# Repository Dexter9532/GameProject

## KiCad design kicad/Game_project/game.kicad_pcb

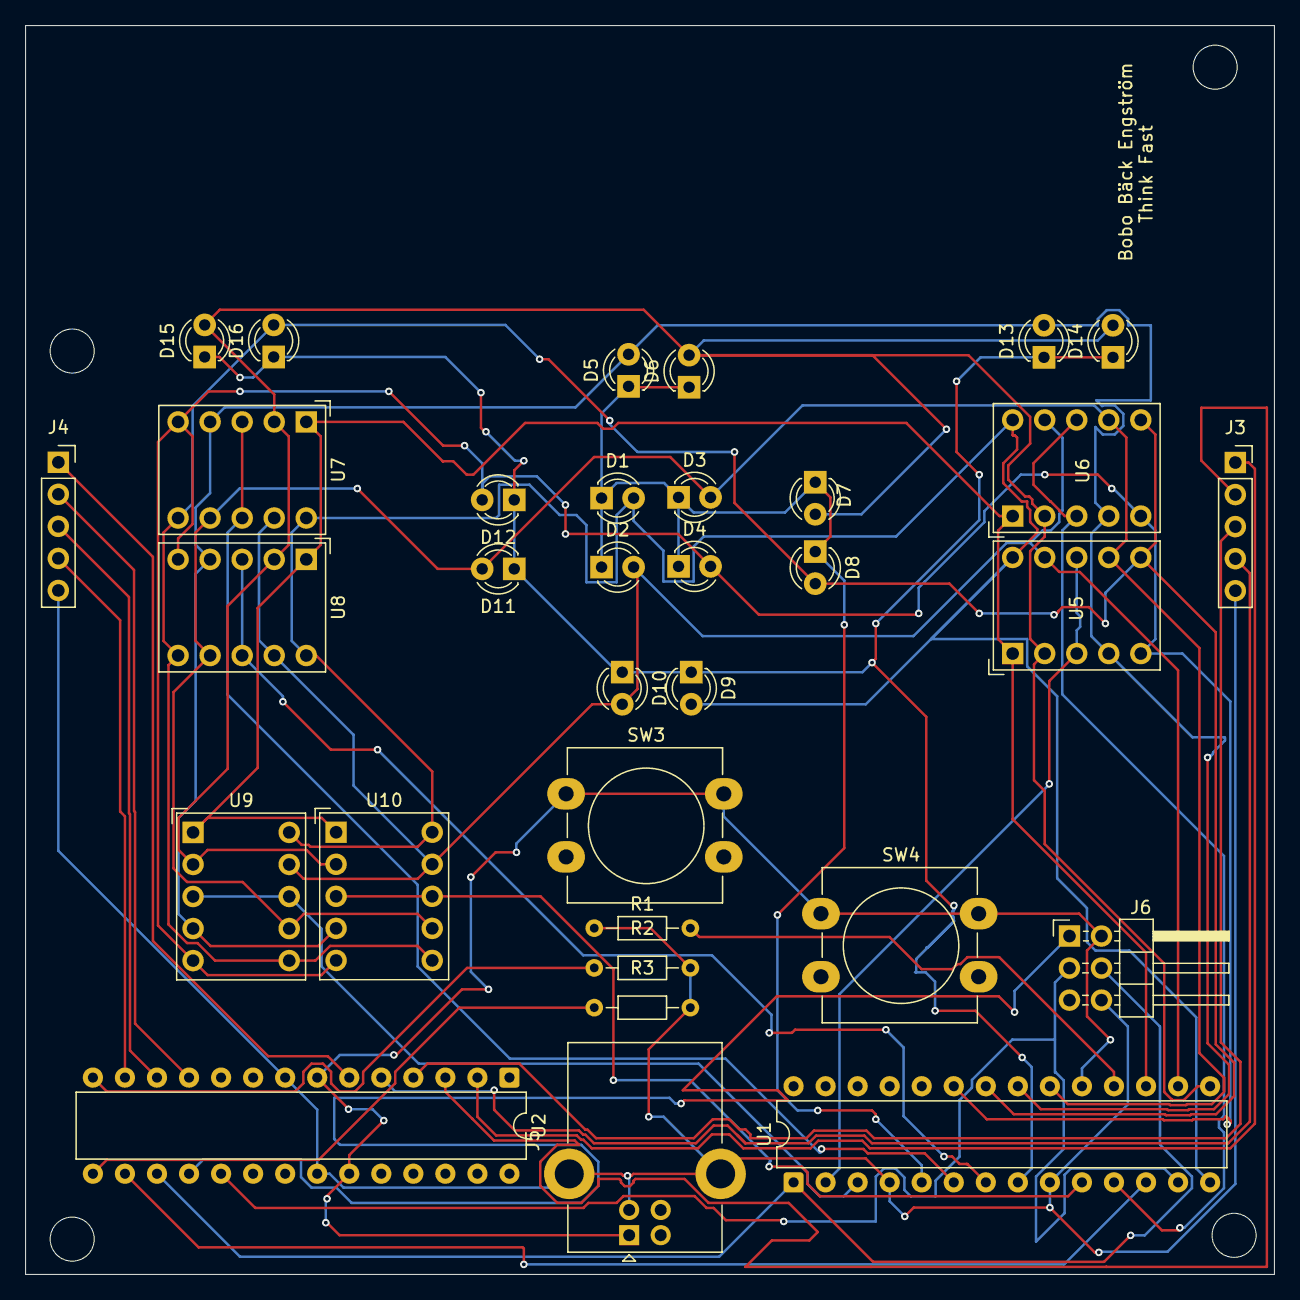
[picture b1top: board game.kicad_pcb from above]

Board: 2 copper layers, 99.0 x 99.0 mm, 33 parts (0 on the bottom side), 33 nets.

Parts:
D1, D2, D3, D4, D5, D6, D7, D8, D9, D10, D11, D12, D13, D14, D15, D16: LED; LED_D3.0mm_Clear
J3, J4: Conn_01x05_Socket; PinSocket_1x05_P2.54mm_Vertical
J5: USB_B; USB_B_Lumberg_2411_02_Horizontal
J6: ISP header; PinHeader_2x03_P2.54mm_Horizontal
R1, R2, R3: 10k; R_Axial_DIN0204_L3.6mm_D1.6mm_P7.62mm_Horizontal
SW3, SW4: SW_pin12; SW_PUSH-12mm_Wuerth-430476085716
U1: MAX7219; DIP-28_W7.62mm
U2: ATmega328P-P; DIP-28_W7.62mm
U5, U6, U7, U8, U9, U10: HDSP-7403; Sx39-1xxxxx

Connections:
+5V: J5.1 (VBUS), J6.2, SW3.1, SW4.1, U1.19 (V+), U2.7 (VCC), U2.23 (PC0)
/A: D1.2 (A), D9.2 (A), U1.14 (SEG_A), U5.10 (A), U6.10 (A), U7.10 (A), U8.10 (A), U9.10 (A), U10.10 (A)
/B: D2.2 (A), D10.2 (A), U1.16 (SEG_B), U5.9 (B), U6.9 (B), U7.9 (B), U8.9 (B), U9.9 (B), U10.9 (B)
/C: D3.2 (A), D11.2 (A), U1.20 (SEG_C), U5.7 (C), U6.7 (C), U7.7 (C), U8.7 (C), U9.7 (C), U10.7 (C)
/D: D4.2 (A), D12.2 (A), U1.23 (SEG_D), U5.5 (D), U6.5 (D), U7.5 (D), U8.5 (D), U9.5 (D), U10.5 (D)
/DIG0: U1.2 (DIG_0), U5.3 (GND), U5.8 (GND)
/DIG1: U1.11 (DIG_1), U6.3 (GND), U6.8 (GND)
/DIG2: U1.6 (DIG_2), U7.3 (GND), U7.8 (GND)
/DIG3: U1.7 (DIG_3), U8.3 (GND), U8.8 (GND)
/DIG4: U1.3 (DIG_4), U9.3 (GND), U9.8 (GND)
/DIG5: U1.10 (DIG_5), U10.3 (GND), U10.8 (GND)
/DIG6: D1.1 (K), D2.1 (K), D3.1 (K), D4.1 (K), D5.1 (K), D6.1 (K), D7.1 (K), D8.1 (K), U1.5 (DIG_6)
/DIG7: D9.1 (K), D10.1 (K), D11.1 (K), D12.1 (K), D13.1 (K), D14.1 (K), D15.1 (K), D16.1 (K), U1.8 (DIG_7)
/DP: D8.2 (A), D16.2 (A), U1.22 (SEG_DP), U5.6 (DP), U6.6 (DP), U7.6 (DP), U8.6 (DP), U9.6 (DP), U10.6 (DP)
/E: D5.2 (A), D13.2 (A), U1.21 (SEG_E), U5.4 (E), U6.4 (E), U7.4 (E), U8.4 (E), U9.4 (E), U10.4 (E)
/F: D6.2 (A), D7.2 (A), D14.2 (A), D15.2 (A), U1.15 (SEG_F), U5.2 (F), U6.2 (F), U7.2 (F), U8.2 (F), U9.2 (F), U10.2 (F)
/G: U1.17 (SEG_G), U5.1 (G), U6.1 (G), U7.1 (G), U8.1 (G), U9.1 (G), U10.1 (G)
/LOAD: U1.12 (LOAD), U2.16 (PB2)
/PB0: R2.1, U2.14 (PB0)
/PB1: R3.1, U2.15 (PB1)
/PD0: J3.1, U2.2 (PD0)
/PD1: J3.2, U2.3 (PD1)
/PD2: J3.3, U2.4 (PD2)
/PD3: J3.4, U2.5 (PD3)
/PD4: J4.1, U2.6 (PD4)
/PD5: J4.2, U2.11 (PD5)
/PD6: J4.3, U2.12 (PD6)
/PD7: J4.4, U2.13 (PD7)
GND: J3.5, J4.5, J5.4 (GND), J5.5 (Shield), J6.6, R1.1, R2.2, R3.2, U1.4 (GND), U1.9 (GND), U2.8 (GND), U2.22 (GND)
MISO: J6.1, U2.18 (PB4)
MOSI: J6.4, U1.1 (DIN), U2.17 (PB3)
unnamed: R1.2, U1.18 (ISET)
SCK: J6.3, U1.13 (CLK), U2.19 (PB5)

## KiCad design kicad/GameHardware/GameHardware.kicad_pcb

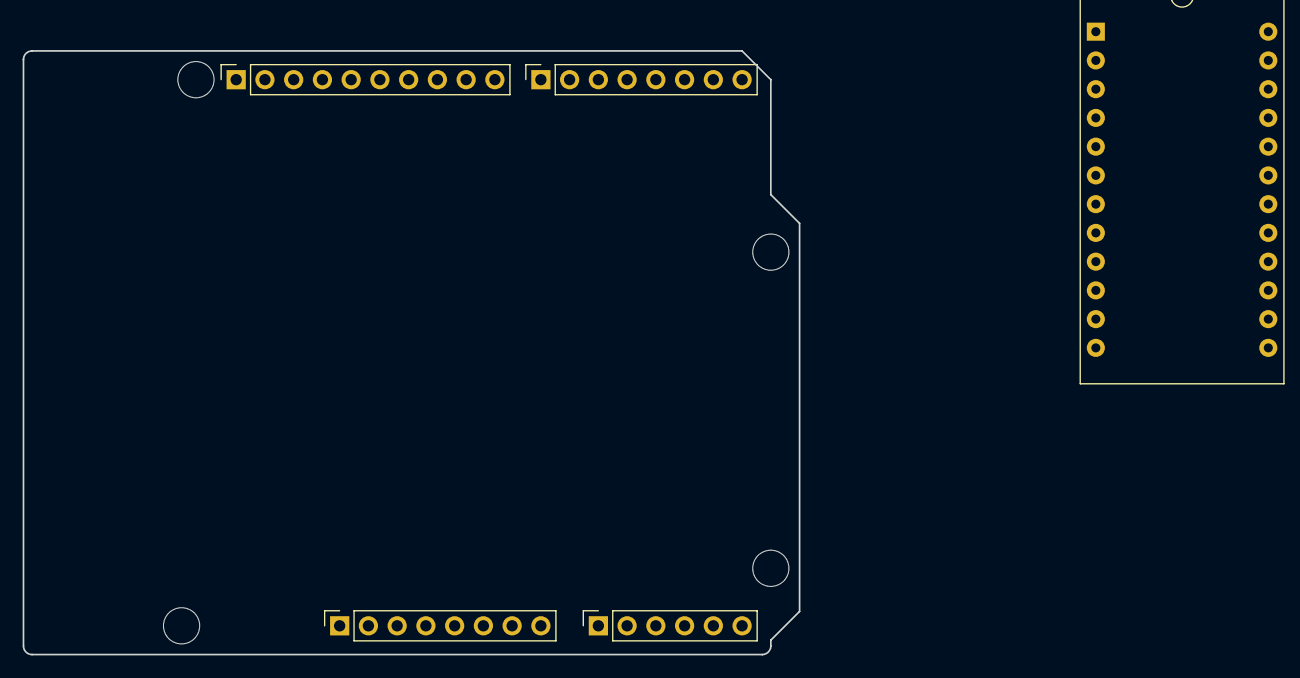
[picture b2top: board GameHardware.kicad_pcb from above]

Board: 2 copper layers, 68.6 x 53.3 mm, 9 parts (0 on the bottom side), 4 nets, no tracks yet.

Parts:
J1: Power; PinSocket_1x08_P2.54mm_Vertical
J2: Digital/PWM; PinSocket_1x10_P2.54mm_Vertical
J3: Analog; PinSocket_1x06_P2.54mm_Vertical
J4: Digital/PWM; PinSocket_1x08_P2.54mm_Vertical
MH1, MH2, MH3, MH4: MountingHole_3.2mm
U1: MAX7219; DIP-24_18.0mmx34.29mm_W15.24mm

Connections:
/SCL/A5: J2.1, J3.6
/SDA/A4: J2.2, J3.5
GND: J1.6, J1.7, J2.4
unnamed: U1.4 (GND), U1.9 (GND)

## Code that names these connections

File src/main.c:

#define F_CPU 1000000UL
#include <avr/io.h>
#include <avr/interrupt.h>
#include <stdint.h>
#include <stdbool.h>
#include <util/delay.h>
#include <stdlib.h>
#include <time.h>

#define CS 2   // PB2 (CS/LOAD)
#define PB0 0
#define PB3 3
#define PB5 5


// Variabler

uint8_t p1_points, p2_points, random_value, buttons_pressed, wheel;
uint8_t right_bin1 = 0b10000000, right_bin2 = 0b01100000, right_bin3 = 0b10110000, right_bin4 = 0b11110000;

uint16_t wait;

bool game_state = false, game_win = false;
bool interrupt_flag = false;

// Funktioner

ISR(PCINT2_vect) {

    buttons_pressed = ~PIND; // Läs in knapptryckningar

    switch (buttons_pressed) {
        case 0b00000100: buttons_pressed = 3; break;
        case 0b00001000: buttons_pressed = 4; break;
        case 0b00010000: buttons_pressed = 5; break;
        case 0b00100000: buttons_pressed = 6; break;
        case 0b01000000: buttons_pressed = 7; break;
        case 0b10000000: buttons_pressed = 8; break;
    }
    // Kontrollera vilken spelare och om svaret är rätt
    switch (buttons_pressed) {
        case 1: case 2: case 3: case 4: // Spelare 1 knappar
<<<<<<< HEAD
        if (buttons_pressed == random_value) {
            p1_points++;
            points();
            } else if (p1_points > 0) { // Se till att poängen inte blir negativ
            p1_points--;
            points();
        }
        execute(0x00, p1_points);
        break;

        case 5: case 6: case 7: case 8: // Spelare 2 knappar
        if (buttons_pressed == (random_value + 4)) {
            p2_points++;
            points();
            } else if (p2_points > 0) {
            p2_points--;
            points();
        }
        execute(0x03, p2_points);
        break;
=======
            if (buttons_pressed == random_value) {
                p1_points++;
                points();
            } else if (p1_points > 0) { // Se till att poängen inte blir negativ
                p1_points--;
                points();
            }
            execute(0x00, p1_points);
            break;

        case 5: case 6: case 7: case 8: // Spelare 2 knappar
            if (buttons_pressed == (random_value + 4)) {
                p2_points++;
                points();
            } else if (p2_points > 0) {
                p2_points--;
                points();
            }
            execute(0x03, p2_points);
            break;
>>>>>>> origin/main
    }

    interrupt_flag = true; // Flagga för att spelet vet att en knapp trycktes
}
void execute(uint8_t cmd, uint8_t data)
{
    PORTB &= ~(1 << CS); // CS LOW (starta överföring)

    SPDR = cmd;  // Skicka kommando
    while (!(SPSR & (1 << SPIF))); // Vänta på överföring klar

    SPDR = data; // Skicka data
    while (!(SPSR & (1 << SPIF))); // Vänta på överföring klar

    PORTB |= (1 << CS); // CS HIGH (slut på överföring)
}
void setup_interrupts() {
    cli();
    PCICR |= (1 << PCIE2);
    PCMSK2 |= 0xFF;
    sei();
}

void spi_init(){
    
    PORTB |= (1 << CS); // CS börjar HIGH (inaktiv)
    // SPI inställningar: Enable SPI, Master mode, SCK = F_CPU/16
    SPCR = (1 << SPE) | (1 << MSTR); // SPI på, master, stigande flank

    execute(0x09, 0b00111111); // Aktiverar decode för DIG0 - DIG5, ingen decode på DIG6-7
    execute(0x0B, 0x07); // hur många används
    execute(0x0A, 0x05); // ljusstyrka
    execute(0x0C, 0x01); // Slå på MAX7221
}
void ADC_init() {
    ADMUX = (1 << REFS0); // Välj referensspänning AVCC (5V)
    ADCSRA = (1 << ADEN) | (1 << ADPS2) | (1 << ADPS1) | (1 << ADPS0);
    // Aktivera ADC och sätt prescaler till 128 (16MHz/128 = 125kHz ADC-klocka)
}
uint16_t ADC_read() {
    ADCSRA |= (1 << ADSC); // Starta ADC-konvertering
    while (ADCSRA & (1 << ADSC)); // Vänta tills konvertering är klar
    return ADC; // Returnera 10-bitars ADC-värde (0–1023)
}
float ADC_getVoltage() {
    uint16_t adc_value = ADC_read();
    float voltage = (adc_value * 5.0) / 1023.0; // Beräkna spänning i volt
    return voltage;
}
uint8_t get_random_decimal() {
    uint16_t adc_value = ADC_read(); // Läs ADC (0 - 1023)
    
    int last_digit = (adc_value % 4) + 1; // Mappa till 1–4

    return last_digit;
}
uint8_t get_random_decimal_extended() {
    uint16_t adc_value = ADC_read(); // Läs ADC (0 - 1023)
    
    uint8_t mapped_value = (adc_value % 11) + 3; // Mappa till 3–13

    return mapped_value;
}
void random_wait() {

    uint8_t random_wait_time = get_random_decimal_extended();
    random_wait_time = (random_wait_time * 1000); // Omvandla till millisekunder
    
    for (uint16_t i = 0; i < random_wait_time; i++) {
        _delay_ms(1);
    }
}
void show_random_number (){
    
    random_wait();

    switch (random_value)
    {
        case 1:
        execute(0x06, right_bin1);
        break;
        case 2:
        execute(0x06, right_bin2);
        break;
        case 3:
        execute(0x06, right_bin3);
        break;
        case 4:
        execute(0x06, right_bin4);
        break;
        // Vänta på interrupt innan spelet fortsätter
    }
    sei();
    interrupt_flag = false; // Återställ flaggan
    while (!interrupt_flag){
        wheel++;
        if (wheel > 20) {
            wheel = 0;
        }
    } // Vänta på att en interrupt händer
<<<<<<< HEAD
=======
}
void points (){
    
    if (p1_points == 10){
        execute(0x00,1);
        execute(0x01,0);
        game_win = true;
    }  
    else if (p2_points == 10){
        execute(0x02,1)
        execute(0x03,0)
        game_win = true;
    }
    if (game_win == false){
    execute(0x01,p1_points);
    execute(0x03,p2_points);
>>>>>>> origin/main
}
void points (){
    
    if (p1_points == 10){
        execute(0x00,1);
        execute(0x01,0);
        game_win = true;
    }
    else if (p2_points == 10){
        execute(0x02,1);
        execute(0x03,0);
        game_win = true;
    }
    if (game_win == false){
        execute(0x01,p1_points);
        execute(0x03,p2_points);
    }
}    
    void reset_game() {
        p1_points = 0;
        p2_points = 0;
        game_state = false;

<<<<<<< HEAD
        //fix this function so it does not restart directly
        _delay_ms(3000);
    }
    int main(void)
=======
    //fix this function so it does not restart directly
    blink_leds();
    _delay_ms(3000);
}
int main(void)
{
    DDRD = 0;
    PORTD = 255;
    DDRB = (1 << PB3) | (1 << PB5) | (1 << CS);

    spi_init();
    ADC_init();
    setup_interrupts();

    while (1)
>>>>>>> origin/main
    {
        DDRD = 0;
        PORTD = 255;
        DDRB = (1 << PB3) | (1 << PB5) | (1 << CS);

        spi_init();
        ADC_init();
        setup_interrupts();

        while (1)
        {
            cli();
            execute(0x09, 0b00111010);
            //show p1 and p2
            execute(0x00,0b11100100);
            execute(0x01,1);
            execute(0x02,0b11100100);
            execute(0x03,2);

<<<<<<< HEAD
            //bestäm hur långt spelet ska vara

            // Check if pin 0 on PORTB is on
            while (!(PINB & (1 << PB0) || game_state == true))
=======
        while (game_win == true)
        {
            uint8_t first = counter / 10;  // Tiotal
            uint8_t second = counter % 10;   // Ental
            execute(0x04, first); // Skicka tiotal
            execute(0x05, second); // Skicka ental
            _delay_ms(10000);
            game_win = false;
            reset_game();
        }
            if (PINB & (1 << PB0))
>>>>>>> origin/main
            {
                cli();
                execute(0x09, 0b00111111);
                game_state = true;

                while (game_win == true)
                {
                    uint8_t first = wheel / 10;  // Tiotal
                    uint8_t second = wheel % 10;   // Ental
                    execute(0x04, first); // Skicka tiotal
                    execute(0x05, second); // Skicka ental
                    _delay_ms(10000);
                    game_win = false;
                    reset_game();
                }
                if (PINB & (1 << PB0))
                {
                    game_state = false;
                    _delay_ms(3000);
                }
                random_value = get_random_decimal();
                show_random_number();
            }
        }
    }

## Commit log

2025-02-18 startup
2025-02-19 added code from microship studio
2025-02-20 Har nu lagt till och startat ett kicad projekt för spelet.
2025-02-20 no succses
2025-02-20 pill
2025-02-21 changed to esp32
2025-02-21 more kicad
2025-02-21 new kicad
2025-02-21 started i pcb
2025-02-21 snart klar i kicad de ska bara rotas
2025-02-21 tests
2025-02-23 some fun
2025-02-24 Auto stash before merge of "main" and "origin/main"
2025-02-25 kicad is done!
2025-02-26 orded
2025-02-28 started to do some code
2025-02-28 code
2025-03-01 find wrong
2025-03-06 much fun things is done today
